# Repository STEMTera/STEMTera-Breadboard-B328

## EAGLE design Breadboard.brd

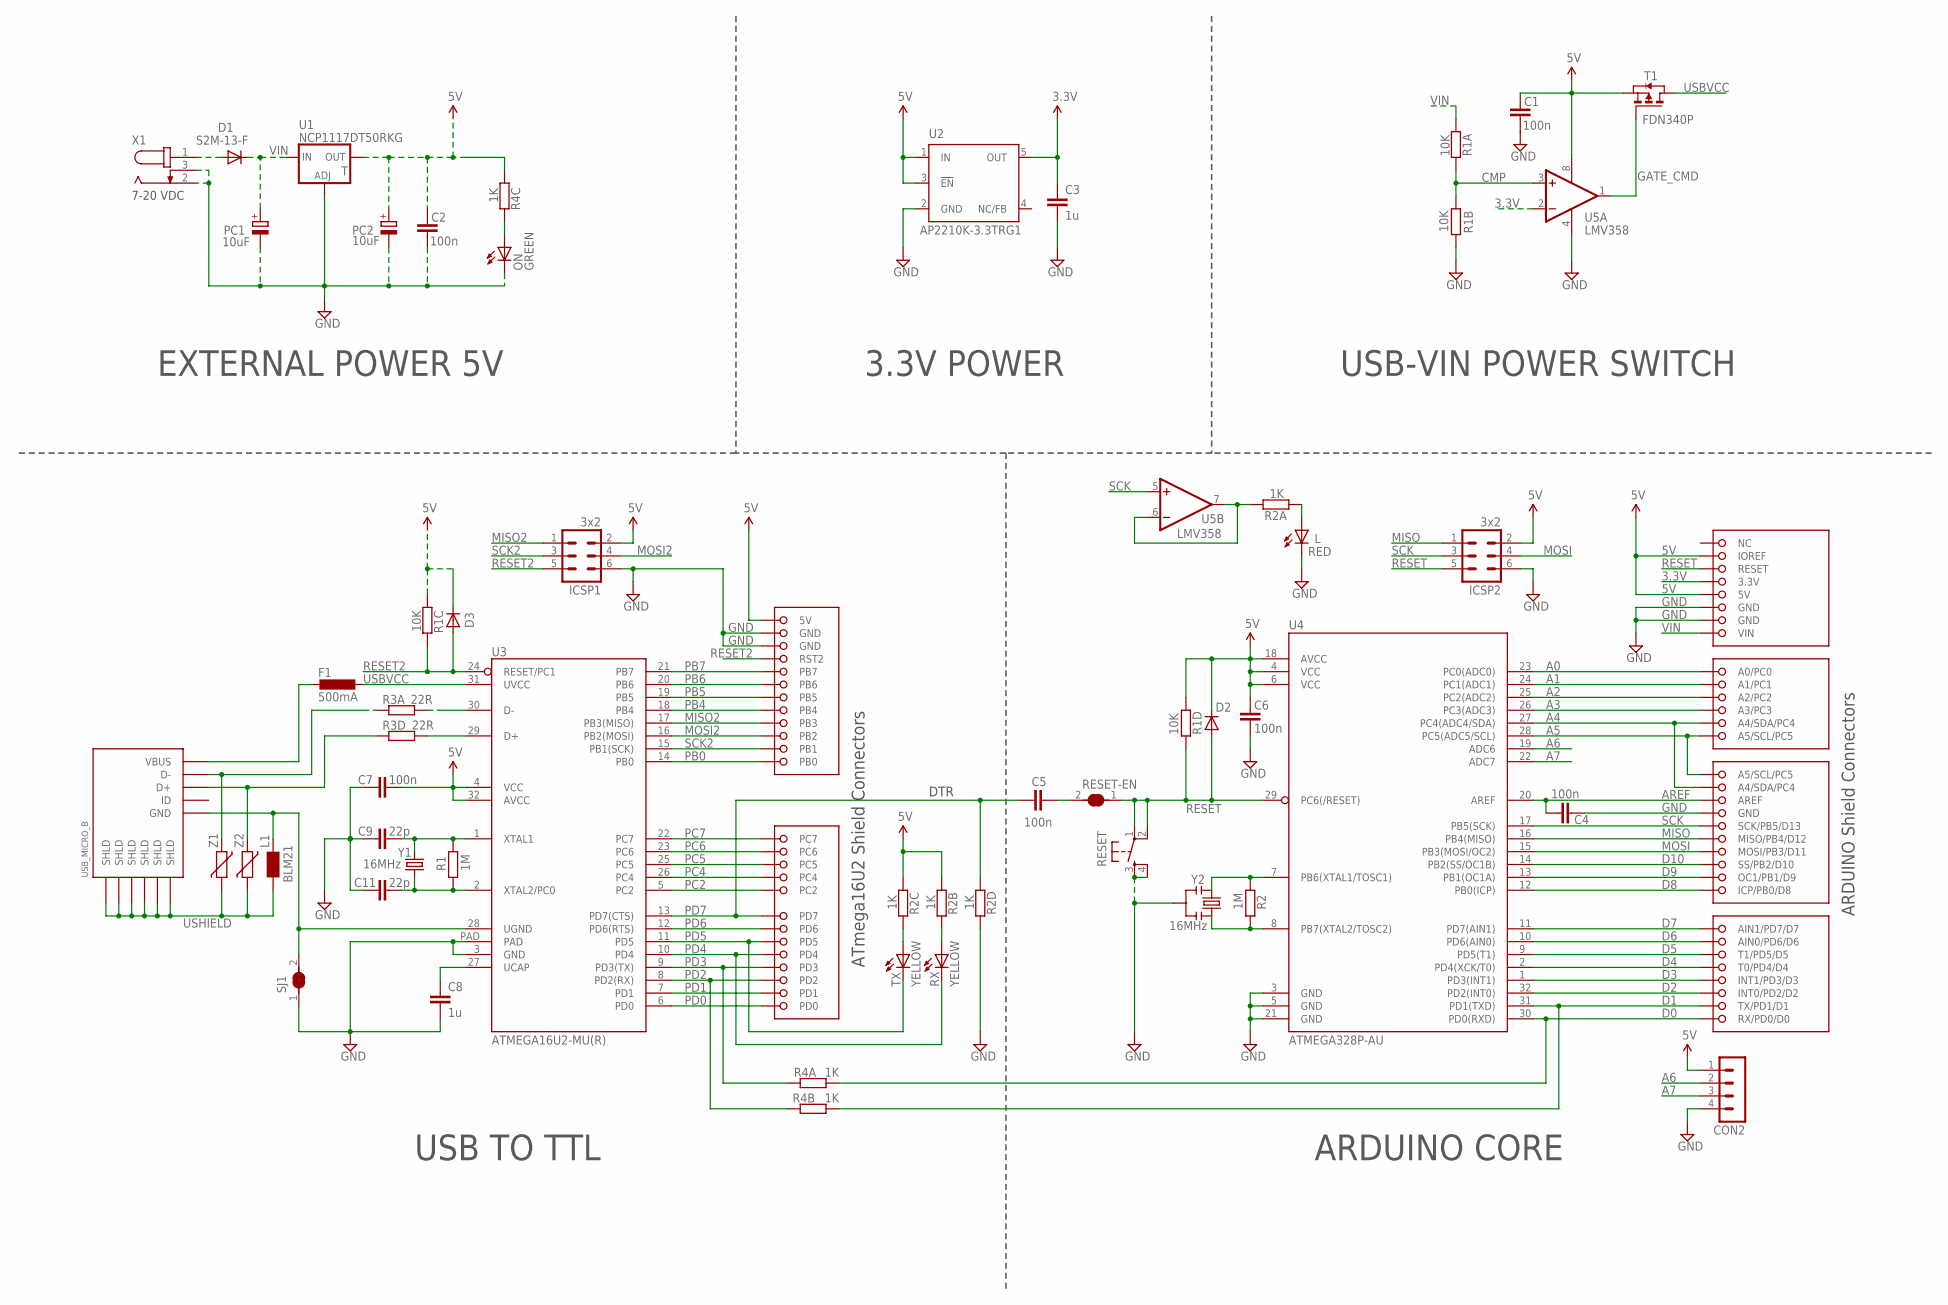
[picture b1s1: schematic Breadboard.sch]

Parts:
C1, C2, C4, C5, C6, C7: 100n; C0603; MPN CC0603KRX7R9BB104
C3, C8: 1u; C0603; MPN CC0603KRX5R6BB105
C9, C11: 22p; C0603; MPN 06035A220JAT2A
CON1: STEMTERA; MPN NOT INSTALLED
CON2: MA04-1; MA04-1-SMD
D1: S2M-13-F; SMB; MPN S2M-13-F
D2, D3: CD1206-S01575; MINIMELF; MPN CD1206-S01575
F1: 500mA; L1812; MPN MF-MSMF050-2
ICSP1, ICSP2: 3x2; MA03-2; MPN NOT INSTALLED
L: RED; LED3MM; MPN L-13ID
L1: BLM21; 0805; MPN BLM21PG221SN1D
ON: GREEN; LED3MM; MPN L-13GD
PC1, PC2: 10uF; CT6032; MPN T491C106M025AT7280
R1, R2: 1M; R0603; MPN RC0603FR-071ML
R1A, R1B, R1C, R1D: 10K; R0603; MPN RC0603FR-0710KL
R2A, R2B, R2C, R2D, R4A, R4B, R4C: 1K; R0603; MPN RC0603FR-071KL
R3A, R3D: 22R; R0603; MPN RC0603FR-0722RL
RESET: PUSH_BUTTON-ESWITCH_TL6120DF300QG
RESET-EN: Jumper; SOLDER_JUMPER_NC; MPN NOT INSTALLED
RX: YELLOW; LED3MM; MPN L-13YD
SJ1: Jumper; SOLDER_JUMPER_NC; MPN NOT INSTALLED
T1: FDN340P; SOT-23; MPN FDN340P
TX: YELLOW; LED3MM; MPN L-13YD
U1: NCP1117DT50RKG; DPACK; MPN NCP1117DT50RKG
U2: AP2210K-3.3TRG1; SOT23-DBV; MPN AP2210K-3.3TRG1
U3: ATMEGA16U2-MU(R); QFN32; MPN ATMEGA16U2-MU
U4: ATMEGA328P-AU; TQFP32-7MM_0.8MM; MPN ATmega328P-AUR
U5: LMV358; SOIC08_3.8MM; MPN LMV358SG-13
USB_MICRO_B: CONN_USB-FCI_10118193-0001LF; CONN_USB_MICRO_B_10118193-0001LF; MPN 10118193-0001LF
X1: CONN_JACK-SINGLE_SIDED; CONN_JACK_PJ-051A-SINGLE_SIDED
Y1: 16MHz; HC49US-SMD-2.5MM; MPN ABLS3-16.000MHZ-D4Y-T
Y2: 16MHz; CSTCE_V; MPN CSTCE16M0V53-R0
Z1, Z2: VARISTORCN0603; CT/CN0603; MPN CG0603MLC-05E

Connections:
3.3V: C3.1, CON1.3.3V, U2.5 (OUT), U5.2 (-IN)
5V: C1.2, C2.2, C6.2, C7.2, CON1.5V, CON1.5V@11 (5V), CON1.IOREF, CON2.1, D2.C, D3.C, ICSP1.2, ICSP2.2, PC2.+, R1C.2, R1D.2, R2B.2, R2C.2, R4C.2, T1.2 (S), U1.4 (OUT), U2.1 (IN), U2.3 (!EN), U3.4 (VCC), U3.32 (AVCC), U4.4 (VCC), U4.6 (VCC), U4.18 (AVCC), U5.8 (V+)
A0: CON1.A0 (A0/PC0), U4.23 (PC0(ADC0))
A1: CON1.A1 (A1/PC1), U4.24 (PC1(ADC1))
A2: CON1.A2 (A2/PC2), U4.25 (PC2(ADC2))
A3: CON1.A3 (A3/PC3), U4.26 (PC3(ADC3))
A4: CON1.A4@1 (A4/SDA/PC4), CON1.A4@2 (A4/SDA/PC4), U4.27 (PC4(ADC4/SDA))
A5: CON1.A5@1 (A5/SCL/PC5), CON1.A5@2 (A5/SCL/PC5), U4.28 (PC5(ADC5/SCL))
A6: CON2.2, U4.19 (ADC6)
A7: CON2.3, U4.22 (ADC7)
AREF: C4.2, CON1.AREF, U4.20 (AREF)
CMP: R1A.1, R1B.2, U5.3 (+IN)
D0: CON1.D0 (RX/PD0/D0), R4A.2, U4.30 (PD0(RXD))
D1: CON1.D1 (TX/PD1/D1), R4B.2, U4.31 (PD1(TXD))
D2: CON1.D2 (INT0/PD2/D2), U4.32 (PD2(INT0))
D3: CON1.D3 (INT1/PD3/D3), U4.1 (PD3(INT1))
D4: CON1.D4 (T0/PD4/D4), U4.2 (PD4(XCK/T0))
D5: CON1.D5 (T1/PD5/D5), U4.9 (PD5(T1))
D6: CON1.D6 (AIN0/PD6/D6), U4.10 (PD6(AIN0))
D7: CON1.D7 (AIN1/PD7/D7), U4.11 (PD7(AIN1))
D8: CON1.D8 (ICP/PB0/D8), U4.12 (PB0(ICP))
D9: CON1.D9 (OC1/PB1/D9), U4.13 (PB1(OC1A))
D10: CON1.D10 (SS/PB2/D10), U4.14 (PB2(SS/OC1B))
GATE_CMD: T1.3 (G), U5.1 (OUT)
GND: C1.1, C2.1, C3.2, C4.1, C6.1, C7.1, C8.2, C9.1, C11.1, CON1.GND@1 (GND), CON1.GND@2 (GND), CON1.GND@3 (GND), CON1.GND@11 (GND), CON1.GND@12 (GND), CON2.4, ICSP1.6, ICSP2.6, L.K (C), ON.K (C), PC1.-, PC2.-, R1B.1, R2D.1, RESET.3, RESET.4, SJ1.1, U1.1 (ADJ), U2.2 (GND), U3.3 (GND), U3.PAD, U4.3 (GND), U4.5 (GND), U4.21 (GND), U5.4 (V-), X1.2, X1.3, Y2.2
MISO: CON1.D12 (MISO/PB4/D12), ICSP2.1, U4.16 (PB4(MISO))
MISO2: CON1.PB3, ICSP1.1, U3.17 (PB3(MISO))
MOSI: CON1.D11 (MOSI/PB3/D11), ICSP2.4, U4.15 (PB3(MOSI/OC2))
MOSI2: CON1.PB2, ICSP1.4, U3.16 (PB2(MOSI))
unnamed: R2.2, U4.7 (PB6(XTAL1/TOSC1)), Y2.1
unnamed: R3A.1, USB_MICRO_B.D-, Z1.1
unnamed: R3D.1, USB_MICRO_B.D+, Z2.1
unnamed: C9.2, R1.2, U3.1 (XTAL1), Y1.2
unnamed: C8.1, U3.27 (UCAP)
unnamed: R3A.2, U3.30 (D-)
unnamed: C11.2, R1.1, U3.2 (XTAL2/PC0), Y1.1
unnamed: R3D.2, U3.29 (D+)
unnamed: R2.1, U4.8 (PB7(XTAL2/TOSC2)), Y2.3
unnamed: R2C.1, TX.A
unnamed: R2B.1, RX.A
unnamed: L.A, R2A.2
unnamed: D1.A, X1.1
unnamed: ON.A, R4C.1
unnamed: C5.2, RESET-EN.2
unnamed: R2A.1, U5.6 (-IN), U5.7 (OUT)
PB0: CON1.PB0, U3.14 (PB0)
PB4: CON1.PB4, U3.18 (PB4)
PB5: CON1.PB5, U3.19 (PB5)
PB6: CON1.PB6, U3.20 (PB6)
PB7: CON1.PB7, U3.21 (PB7)
PC2: CON1.PC2, U3.5 (PC2)
PC4: CON1.PC4, U3.26 (PC4)
PC5: CON1.PC5, U3.25 (PC5)
PC6: CON1.PC6, U3.23 (PC6)
PC7: CON1.PC7, U3.22 (PC7)
PD0: CON1.PD0, U3.6 (PD0)
PD1: CON1.PD1, U3.7 (PD1)
PD2: CON1.PD2, R4B.1, U3.8 (PD2(RX))
PD3: CON1.PD3, R4A.1, U3.9 (PD3(TX))
PD4: CON1.PD4, RX.K (C), U3.10 (PD4)
PD5: CON1.PD5, TX.K (C), U3.11 (PD5)
PD6: CON1.PD6, U3.12 (PD6(RTS))
PD7: C5.1, CON1.PD7, R2D.2, U3.13 (PD7(CTS))
RESET: CON1.RESET, D2.A, ICSP2.5, R1D.1, RESET.1, RESET.2, RESET-EN.1, U4.29 (PC6(/RESET))
RESET2: CON1.RST2, D3.A, ICSP1.5, R1C.1, U3.24 (RESET/PC1)
SCK: CON1.D13 (SCK/PB5/D13), ICSP2.3, U4.17 (PB5(SCK)), U5.5 (+IN)
SCK2: CON1.PB1, ICSP1.3, U3.15 (PB1(SCK))
UGND: L1.1, SJ1.2, U3.28 (UGND), USB_MICRO_B.GND
USBVCC: F1.1, T1.1 (D), U3.31 (UVCC)
USHIELD: L1.2, USB_MICRO_B.SHLD@1 (SHLD), USB_MICRO_B.SHLD@2 (SHLD), USB_MICRO_B.SHLD@3 (SHLD), USB_MICRO_B.SHLD@4 (SHLD), USB_MICRO_B.SHLD@5 (SHLD), USB_MICRO_B.SHLD@6 (SHLD), Z1.2, Z2.2
VBUS: F1.2, USB_MICRO_B.VBUS
VIN: CON1.VIN, D1.C, PC1.+, R1A.2, U1.3 (IN)

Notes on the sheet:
7-20 VDC
EXTERNAL POWER 5V
3.3V POWER
USB-VIN POWER SWITCH
USB TO TTL
ARDUINO CORE
ARDUINO Shield Connectors
ATmega16U2 Shield Connectors
DTR

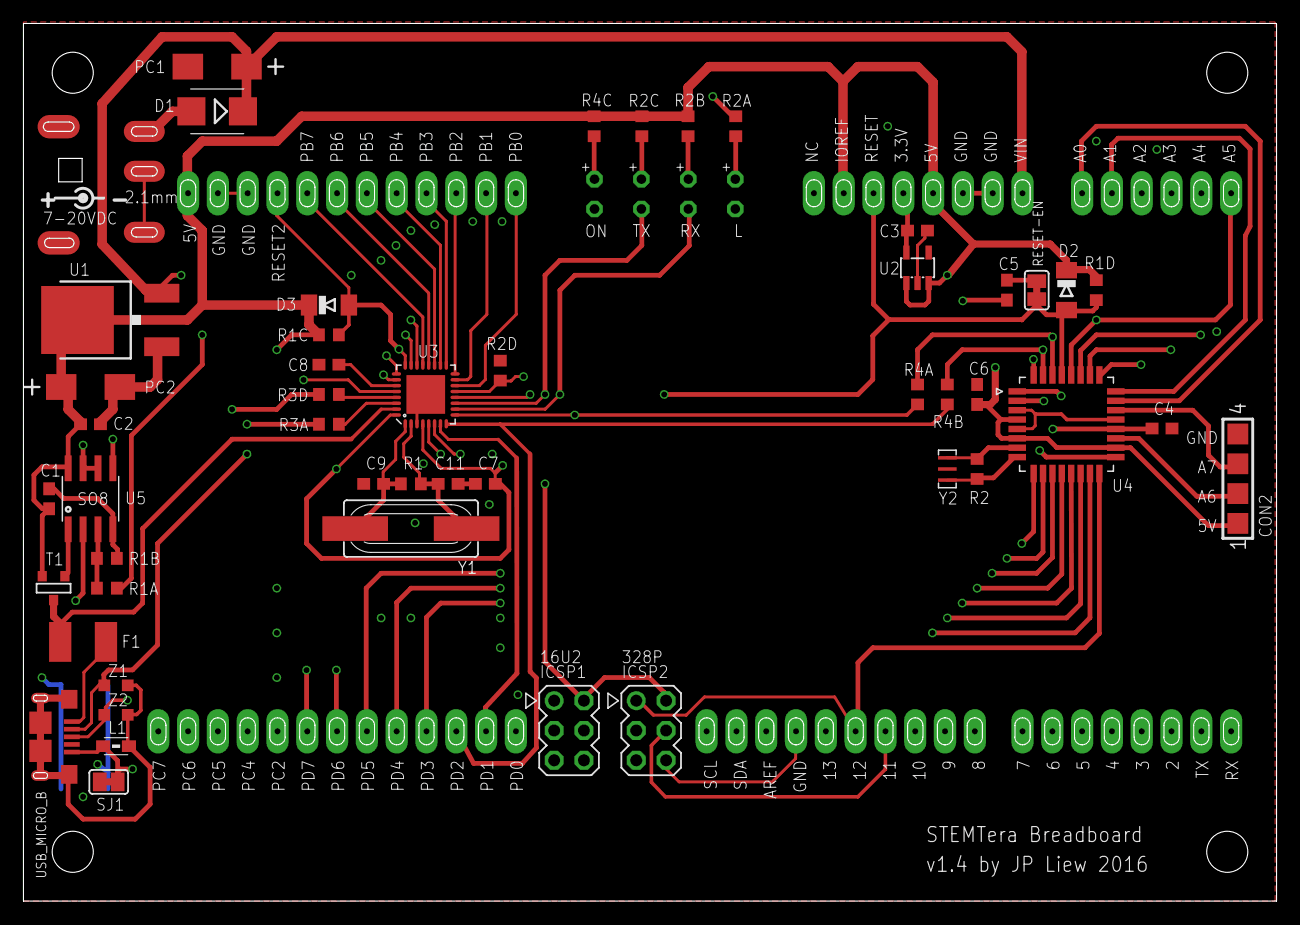
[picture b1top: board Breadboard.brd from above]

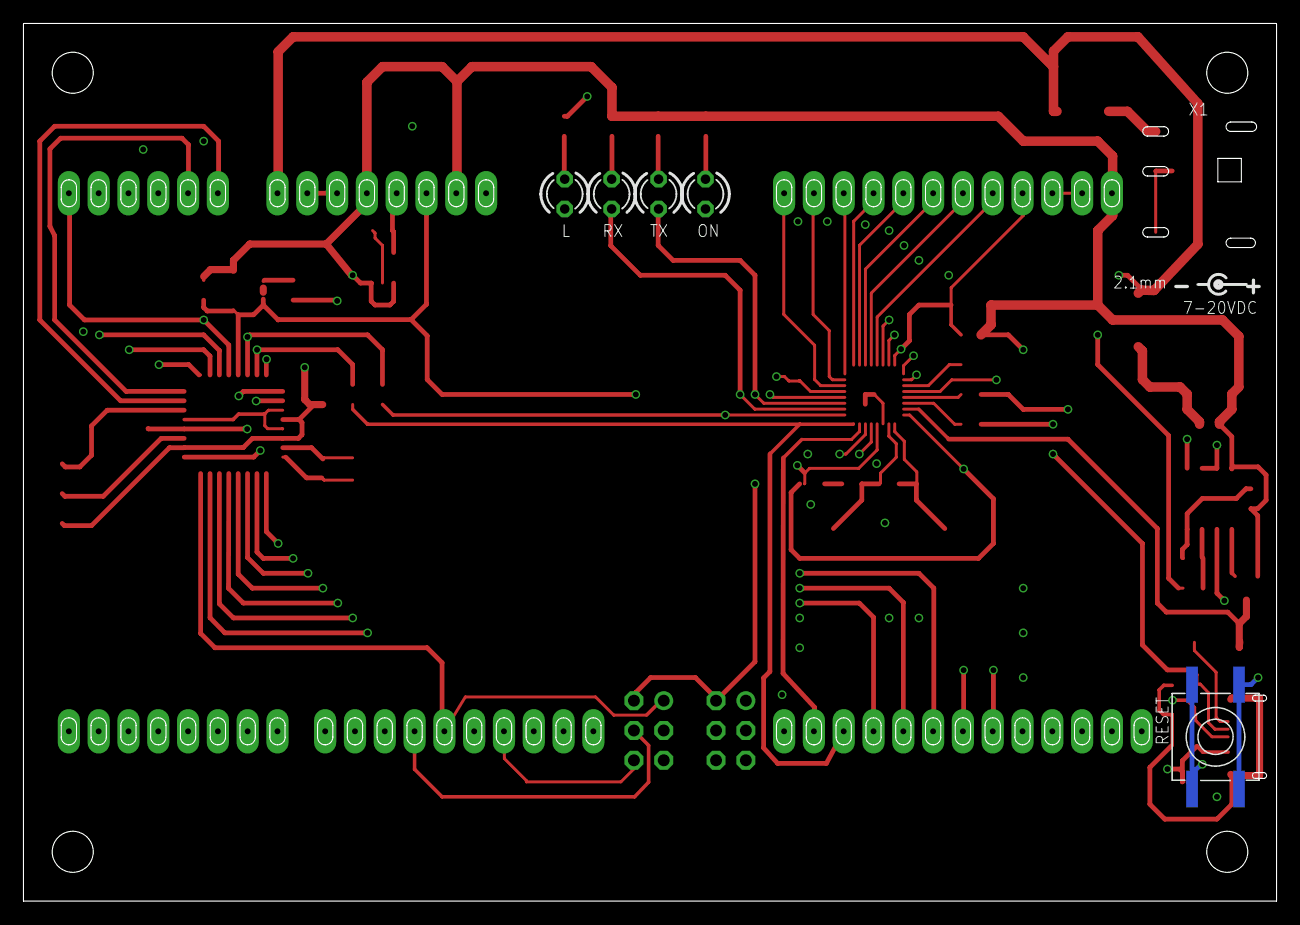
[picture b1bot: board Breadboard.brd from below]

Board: 4 copper layers, 106.8 x 74.8 mm, 55 parts (6 on the bottom side), 72 nets.

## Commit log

2017-02-02 added 3D models, dimension specs
2017-02-02 added library
2017-02-02 added firmware
2017-02-13 added Fritzing Part
2017-02-24 fixed SVG not generated when export in Fritzing
2017-02-25 fixed Fritzing export SVG not aligned
2017-03-09 added ATmega32U2 production firmware
2019-09-04 fixed HEX file last line no CRLF
